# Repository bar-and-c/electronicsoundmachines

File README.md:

# electronicsoundmachines
A collection of stuff related to creating sounds using electronic devices.

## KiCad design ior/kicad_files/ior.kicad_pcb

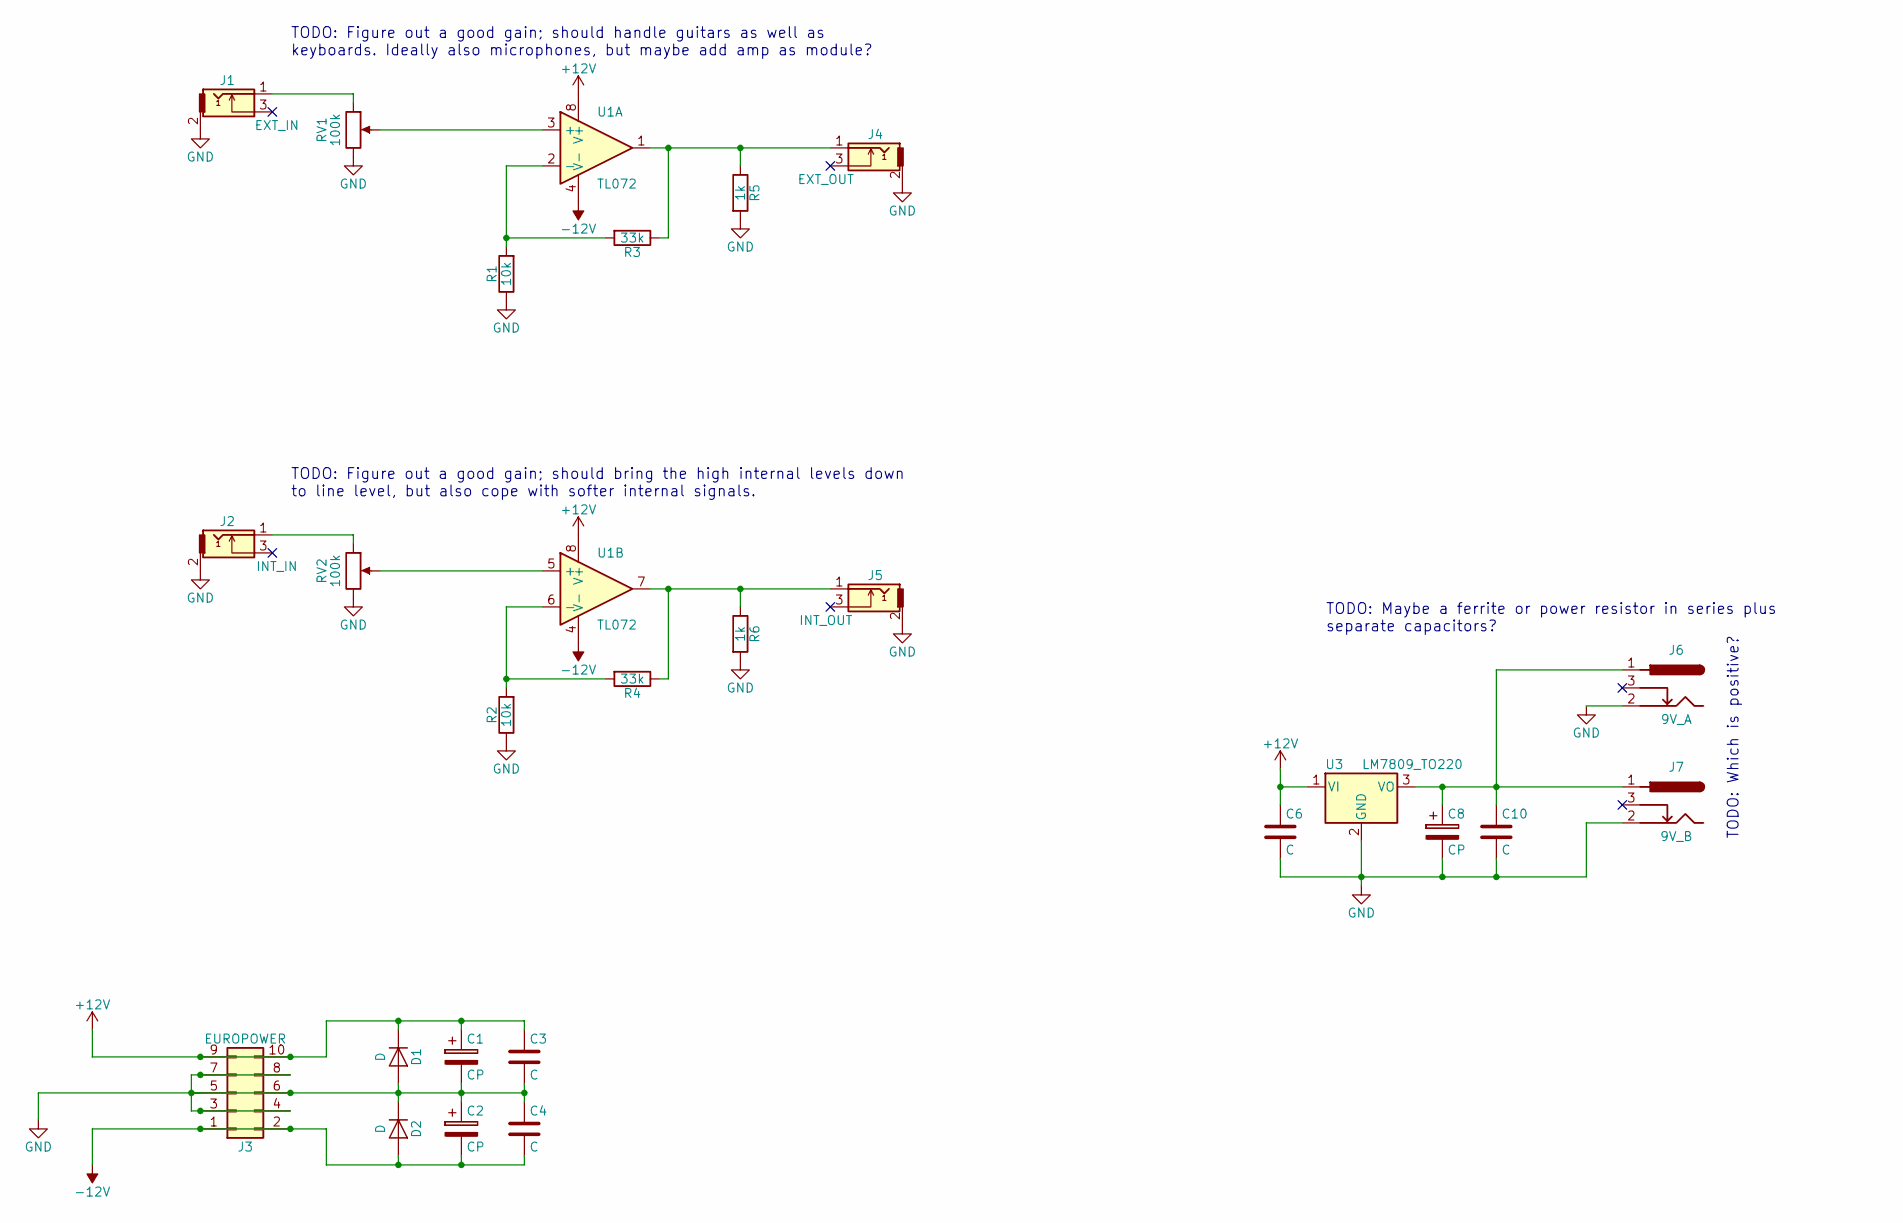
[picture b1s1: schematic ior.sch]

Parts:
C1, C2, C8: CP; CP_Radial_D10.0mm_P2.50mm
C3, C4, C6, C10: C; C_Rect_L7.0mm_W3.5mm_P5.00mm
D1, D2: D; D_DO-35_SOD27_P7.62mm_Horizontal
J1: EXT_IN; Pin_Header_Straight_1x03_Pitch2.54mm
J2: INT_IN; Switchcraft_35RAPC2AV_3_5_mm_jack
J3: EUROPOWER; Pin_Header_Straight_2x05_Pitch2.54mm
J4: EXT_OUT; Switchcraft_35RAPC2AV_3_5_mm_jack
J5: INT_OUT; Pin_Header_Straight_1x03_Pitch2.54mm
J6: 9V_A; BARREL_JACK
J7: 9V_B; BARREL_JACK
R1, R2: 10k; R_Axial_DIN0207_L6.3mm_D2.5mm_P7.62mm_Horizontal
R3, R4: 33k; R_Axial_DIN0207_L6.3mm_D2.5mm_P7.62mm_Horizontal
R5, R6: 1k; R_Axial_DIN0207_L6.3mm_D2.5mm_P7.62mm_Horizontal
RV1, RV2: 100k; Potentiometer_Alps_RK09Y_Vertical
U1: TL072; DIP-8_W7.62mm_Socket_LongPads
U3: LM7809_TO220; TO-220-3_Horizontal

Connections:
+12V: C1.1, C3.1, C6.1, D1.1 (K), J3.9, J3.10, U1.8 (V+), U3.1 (VI)
-12V: C2.2, C4.2, D2.2 (A), J3.1, J3.2, U1.4 (V-)
GND: C1.2, C2.1, C3.2, C4.1, C6.2, C8.2, C10.2, D1.2 (A), D2.1 (K), J1.2, J2.2, J3.3, J3.4, J3.5, J3.6, J3.7, J3.8, J4.2, J5.2, J6.2, J7.2, R1.1, R2.1, R5.2, R6.2, RV1.3, RV2.3, U3.2 (GND)
unnamed: C8.1, C10.1, J6.1, J7.1, U3.3 (VO)
unnamed: J1.1, RV1.1
unnamed: J2.1, RV2.1
unnamed: J4.1, R3.1, R5.1, U1.1
unnamed: J5.1, R4.1, R6.1, U1.7
unnamed: R1.2, R3.2, U1.2 (-)
unnamed: R2.2, R4.2, U1.6 (-)
unnamed: RV1.2, U1.3 (+)
unnamed: RV2.2, U1.5 (+)

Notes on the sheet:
TODO: Which is positive?
TODO: Figure out a good gain; should handle guitars as well as keyboards. Ideally also microphones, but maybe add amp as module?
TODO: Figure out a good gain; should bring the high internal levels down to line level, but also cope with softer internal signals.
TODO: Maybe a ferrite or power resistor in series plus separate capacitors?

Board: 2 copper layers, 26 parts (0 on the bottom side), 12 nets, no tracks yet.

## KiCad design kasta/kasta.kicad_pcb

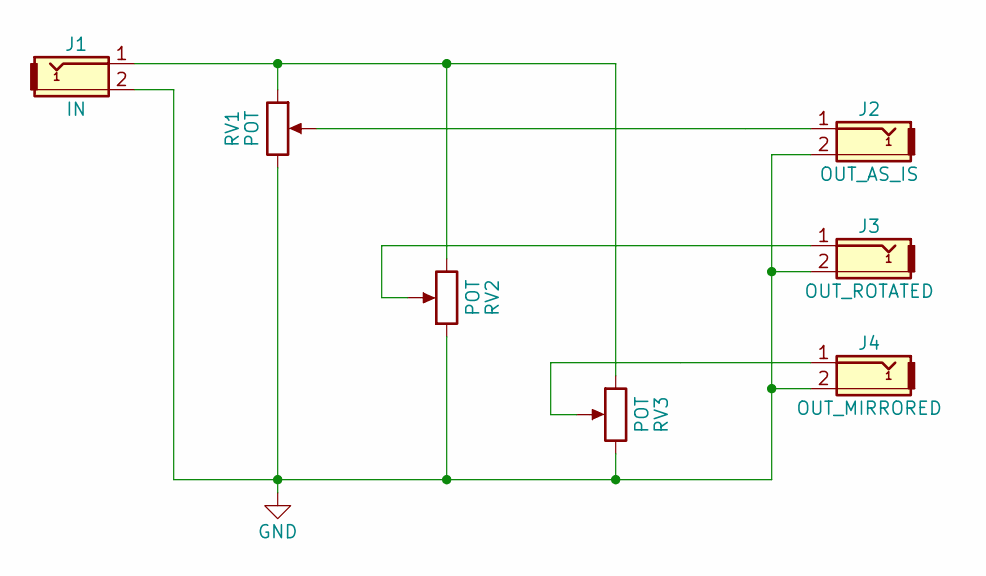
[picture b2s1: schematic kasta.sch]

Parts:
J1: IN; Pin_Header_Straight_1x02_Pitch2.54mm
J2: OUT_AS_IS; Pin_Header_Straight_1x02_Pitch2.54mm
J3: OUT_ROTATED; Pin_Header_Straight_1x02_Pitch2.54mm
J4: OUT_MIRRORED; Pin_Header_Straight_1x02_Pitch2.54mm
RV1, RV2, RV3: POT; Potentiometer_Alps_RK09Y_Vertical

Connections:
GND: J1.2, J2.2, J3.2, J4.2, RV1.3, RV2.1, RV3.3
unnamed: J1.1, RV1.1, RV2.3, RV3.1
unnamed: J2.1, RV1.2
unnamed: J3.1, RV2.2
unnamed: J4.1, RV3.2

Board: 2 copper layers, 7 parts (0 on the bottom side), 5 nets, no tracks yet.

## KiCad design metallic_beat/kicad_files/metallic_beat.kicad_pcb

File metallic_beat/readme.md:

# Metallic Beat

The CR-78 is my favourite drum machine, both the sounds and the patterns (it is like canned musicality), and the cymbal together with metallic beat was the sound(s) I wanted to build first. So far I have only finished the latter. 

The schematic is not completely finished yet, but soundwise it is usable (the final stage will soon be added to the schematic).

In addition to the service manual, lots of inspiration found in <http://electro-music.com/forum/topic-67084-25.html>, especially <http://electro-music.com/forum/phpbb-files/cr78_mb_607.png> (for me, the key to getting that kind of design to work was to lower R566 – I think it was designed to work with a negative trigger pulse).

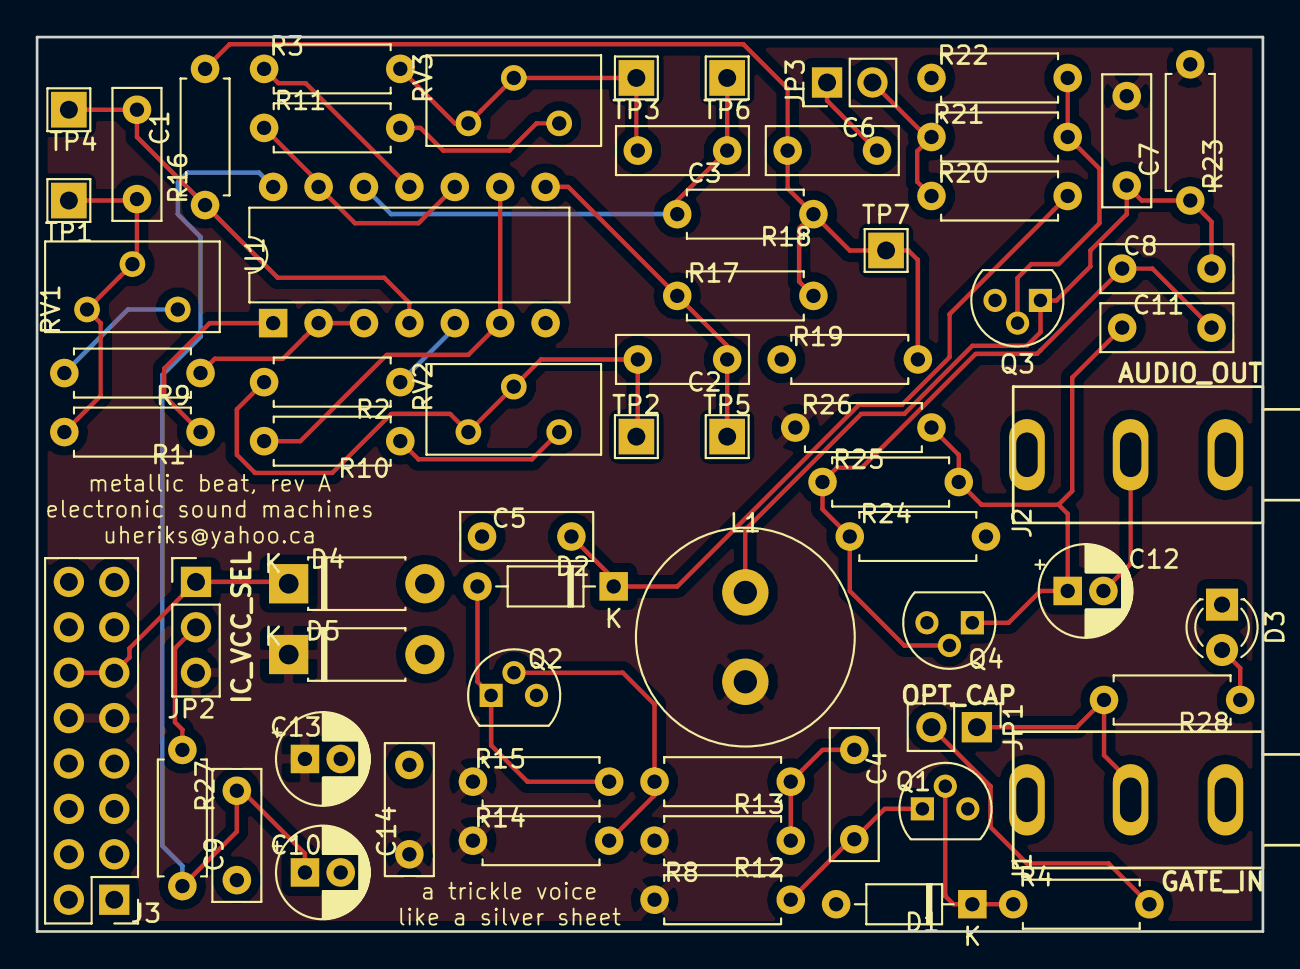
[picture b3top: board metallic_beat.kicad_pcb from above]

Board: 2 copper layers, 68.6 x 50.0 mm, 66 parts (0 on the bottom side), 37 nets.

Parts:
C1: 1.5 nF; C_Rect_L7.2mm_W2.5mm_P5.00mm_FKS2_FKP2_MKS2_MKP2
C2: 1.8 nF; C_Rect_L7.2mm_W2.5mm_P5.00mm_FKS2_FKP2_MKS2_MKP2
C3: 2.2 nF; C_Rect_L7.2mm_W2.5mm_P5.00mm_FKS2_FKP2_MKS2_MKP2
C4: 470 nF; C_Rect_L7.2mm_W2.5mm_P5.00mm_FKS2_FKP2_MKS2_MKP2
C5: 22 nF; C_Rect_L7.2mm_W2.5mm_P5.00mm_FKS2_FKP2_MKS2_MKP2
C6, C7: 15 nF; C_Rect_L7.2mm_W2.5mm_P5.00mm_FKS2_FKP2_MKS2_MKP2
C8: 68nF; C_Rect_L7.2mm_W2.5mm_P5.00mm_FKS2_FKP2_MKS2_MKP2
C9, C14: 100nF; C_Rect_L7.2mm_W2.5mm_P5.00mm_FKS2_FKP2_MKS2_MKP2
C10, C13: 10uF; CP_Radial_D5.0mm_P2.00mm
C11: 100pF; C_Rect_L7.2mm_W2.5mm_P5.00mm_FKS2_FKP2_MKS2_MKP2
C12: 4.7uF; CP_Radial_D5.0mm_P2.00mm
D1, D2: 1N4148; D_DO-35_SOD27_P7.62mm_Horizontal
D3: LOW POWER LED; LED_D3.0mm_FlatTop
D4, D5: 1N4001; D_DO-41_SOD81_P7.62mm_Horizontal
J1: GATE_IN; Switchcraft_35RAPC2AV_3_5_mm_jack_no_switch
J2: AUDIO_OUT; Switchcraft_35RAPC2AV_3_5_mm_jack_no_switch
J3: POWER; PinHeader_2x08_P2.54mm_Vertical
JP1: OPT_CAP; PinHeader_1x02_P2.54mm_Vertical
JP2: IC_VCC_SEL; PinHeader_1x03_P2.54mm_Vertical
JP3: VCA_IN; PinHeader_1x02_P2.54mm_Vertical
L1: 47 mH; L_Radial_D12.0mm_P5.00mm_Fastron_11P
Q1, Q4: BC337; TO-92L
Q2, Q3: BC547; TO-92L
R1, R2, R3, R28: 4.7k; R_Axial_DIN0207_L6.3mm_D2.5mm_P7.62mm_Horizontal
R4: 680; R_Axial_DIN0207_L6.3mm_D2.5mm_P7.62mm_Horizontal
R8: 100k; R_Axial_DIN0207_L6.3mm_D2.5mm_P7.62mm_Horizontal
R9, R10, R11: 39k; R_Axial_DIN0207_L6.3mm_D2.5mm_P7.62mm_Horizontal
R12, R15, R23: 10k; R_Axial_DIN0207_L6.3mm_D2.5mm_P7.62mm_Horizontal
R13: 1k; R_Axial_DIN0207_L6.3mm_D2.5mm_P7.62mm_Horizontal
R14: 820k; R_Axial_DIN0207_L6.3mm_D2.5mm_P7.62mm_Horizontal
R16, R17, R18, R25: 470k; R_Axial_DIN0207_L6.3mm_D2.5mm_P7.62mm_Horizontal
R19: 6.8k; R_Axial_DIN0207_L6.3mm_D2.5mm_P7.62mm_Horizontal
R20: 3.3M; R_Axial_DIN0207_L6.3mm_D2.5mm_P7.62mm_Horizontal
R21: 100K; R_Axial_DIN0207_L6.3mm_D2.5mm_P7.62mm_Horizontal
R22: 270K; R_Axial_DIN0207_L6.3mm_D2.5mm_P7.62mm_Horizontal
R24: 120k; R_Axial_DIN0207_L6.3mm_D2.5mm_P7.62mm_Horizontal
R26: 47k; R_Axial_DIN0207_L6.3mm_D2.5mm_P7.62mm_Horizontal
R27: 47; R_Axial_DIN0207_L6.3mm_D2.5mm_P7.62mm_Horizontal
RV1, RV2, RV3: 20k; Potentiometer_Bourns_3386X_Horizontal
TP1: CAP1; TestPoint_THTPad_2.0x2.0mm_Drill1.0mm
TP2: CAP2; TestPoint_THTPad_2.0x2.0mm_Drill1.0mm
TP3: CAP3; TestPoint_THTPad_2.0x2.0mm_Drill1.0mm
TP4: OSC1; TestPoint_THTPad_2.0x2.0mm_Drill1.0mm
TP5: OSC2; TestPoint_THTPad_2.0x2.0mm_Drill1.0mm
TP6: OSC3; TestPoint_THTPad_2.0x2.0mm_Drill1.0mm
TP7: OSC_OUT; TestPoint_THTPad_2.0x2.0mm_Drill1.0mm
U1: 4069; DIP-14_W7.62mm

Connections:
+5V: D4.1, J3.11, J3.12, JP2.1
+12V: C7.1, C13.1, C14.1, D5.1, J3.9, J3.10, JP2.3, L1.1, R8.1, R12.1, R14.1, R15.1, R23.1, R26.1
GND: C5.1, C9.2, C10.2, C13.2, C14.2, D1.2, D3.1, D4.2, D5.2, J1.2, J2.2, J3.3, J3.4, J3.5, J3.6, J3.7, J3.8, Q1.3, Q2.3, Q3.3, Q4.3, R19.1, R22.2, R24.2, U1.7
unnamed: C1.1, R16.2, TP4.1, U1.4
unnamed: C1.2, R1.2, RV1.1, RV1.2, TP1.1
unnamed: C2.1, R17.2, TP5.1, U1.8
unnamed: C2.2, R2.2, RV2.1, RV2.2, TP2.1
unnamed: C3.1, R18.2, TP6.1, U1.12
unnamed: C3.2, R3.2, RV3.1, RV3.2, TP3.1
unnamed: C4.1, R12.2, R13.2
unnamed: C4.2, Q1.1, R8.2
unnamed: C5.2, D2.1, R20.2
unnamed: C6.1, JP3.1
unnamed: C6.2, R16.1, R17.1, R18.1, R19.2, TP7.1
unnamed: C7.2, C8.2, L1.2, Q3.1, R23.2
unnamed: C9.1, C10.1, R27.2, U1.14
unnamed: C11.1, C12.1, Q4.1, R25.1, R26.2
unnamed: C8.1, C11.2, Q4.2, R24.1, R25.2
unnamed: C12.2, J2.1
unnamed: D1.1, Q1.2, R4.1
unnamed: D2.2, Q2.1, R15.2
unnamed: D3.2, R28.1
unnamed: J1.1, JP1.1, R28.2
unnamed: JP1.2, R4.2
unnamed: JP2.2, R27.1
unnamed: JP3.2, R20.1, R21.2
unnamed: Q2.2, R13.1, R14.2
unnamed: Q3.2, R21.1, R22.1
unnamed: R1.1, U1.1
unnamed: R2.1, U1.5
unnamed: R3.1, U1.11
unnamed: R9.1, U1.2, U1.3
unnamed: R9.2, RV1.3
unnamed: R10.1, U1.6, U1.9
unnamed: R10.2, RV2.3
unnamed: R11.1, U1.10, U1.13
unnamed: R11.2, RV3.3

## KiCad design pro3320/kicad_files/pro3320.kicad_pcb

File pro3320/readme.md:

# pro3320 VCF

This VCF is pretty much only an implementation of the data sheet's reference circuits, with some inspiration taken from the ProOne's schematic. Also, I added four switches, to be able to switch between high pass and low pass filter for each stage.

The things "inspired by" the ProOne include e.g. the OP amp in the resonance chain, and using 150pF instead of 300pF for filter capacitors. The latter shifts the filter frequency one octave up, according to https://electricdruid.net/cem3320-filter-designs/ – try changing them if you feel bold.

I added an optional output after stage two; I figured it would be nice to be be able to get an intermediate signal out (I imagined that would be like a 12dB/octave filter). Something is strange there, though, and I haven't figured out what. It sounds OK without resonance, but with resonance it gets really weird. Quiet. So maybe don't use that output, okay, or be happy using it without resonance?
My uneducated guess is that the resonance feedback is taken from the output, but when tapping from that extra output, the resonance is still taken from the "normal" (24dB/octave) output. I cannot explain what the effect would be as it is, maybe some phase cancellation thing, but that is the only thing I can think of. There are synths that have options like these, see https://electricdruid.net/cem3320-filter-designs/ for examples, and e.g. the Elka Synthex takes the resonance feedback from the actual output.

## Build instructions

### General hints

- If you're using the panel currently in the repo, C1 is too close to the switch SW2, let C1 have a little longer legs than normal, so that you can poke it to the side without force. 
- The jacks are mounted a bit too close to the PCB, risk for contact with pot lugs. Clip the pot lugs (or make another panel design).
- The voltage divider and shit that provides frequency control is a bit off. Possibly because of too high resistance(s), maybe other stuff in parallell is lowering the effective resistance. In any case, either figure out the root cause (which might involve getting other pots), or just experiment to get it as you want (e.g.: if it is as I suspect, that e.g. other impedances in the circuit somehow affect the R1/RV1 voltage divider, then it should be possible to change R1 to something lower instead of changing R1/RV1 to say 12k/10k). I put 100k in parallell with the 120k – thought it might be too much, but it turned out almost OK. The effect in sound, with too little voltage on RV1, is that the filter doesn't open up completely.

## Design woes
After building my first one I quickly realised that I had taken too many shortcuts without thinking when doing the schematic. Things sounded bad, the resonance was dull and strange. On top of that, after measuring to find reasons _why_, suddenly the low pass configuration stopped working altogether – whether because of sloppy measuring damaging the IC, or something else, I do not know. 

What I did discover, though, was that the refernce schematic was designed for +/- 15 volts, and some of the text I skimmed over in a haste the first time through made me realise that most of the resistors in the signal path should have other, lower, values. 

So, this is an attempt to document how I _think_ it should be, for future reference (so that I know what I did, and why).

Alright, first (what I think is) the easy stuff, frequency and resonance control, then on to the slightly more hairy stuff in the signal path. 

### Cutoff frequency control
The frequency control input, pin 12, should be kept between -25mV and 155mV for best results. Also, the in contrast to my intuition, a higher voltage on pin 12 results in a lower filter cutoff. The "absolute maximum ratings" section states that the max voltage between pin 12 and ground is +/-6V. The last fact feels reassuring, it gives a good margin to screw up!
In other words: 
In my schematic, I have one inverting OP-amp stage to convert the incoming CV (as well as the CV from the internal cutoff potentiometer).
The OP-amp stage has an amplification of -0.039, so 0 to 10V in should give 0 to -0.39 volts.

So, the cutoff pot is at the bottom of a voltage divider, making the CV from the pot go from 0 to approx 5.5 volts. With the amplification factor -0.039, that gives roughly 0 to -210mV.

But wait, there's also an offset: a voltage divider that, given the amplification factor, should give a idle voltage of about 250mV on the output, so the internal cutoff pot would give 250mV to 40mV when turning it from low to high cutoff. OK, don't know how I calculated that originally, but hey – it's within reasonable limits. 

The external CV can theoretically be pretty much anything between -12V to 12V, giving an output of approx. 700mV to -200mV, including the offset. Very much outside the "-25mV and 155mV for best results" range, but far from the maximum +/-6V. 

### Resonance control
Maximum limit: +2 to -18 volts to ground. Also, max current for any pin is 40mA.
The control signal is a current input, the input is – as I understand it – virtual ground, meaning the control current can be calculated from the control voltage over the serial resistor (R23 in rev A of the schematic). The resistor should be chosen to give the desired maximum resonance control current at max resonance control voltage. The "desired current" is not obvious (to me); there is a graph, and there is some math, and not until now do I fully understand that I _still_ don't understand how to pick that resistor. Well, guessing is also an option: the reference schematic has 100k for unknown control voltage (but the circuit is based on +/-15V, and for 15V CV, that goves 150uA), the ProOne has 200k for 15V max (giving 75uA). I accidentally envisioned a control voltage between 0-5V and chose 56k to get around 100uA, but for the actual max 12V in, that would give 210uA – which is high, but not freakishly high. Also, for the internal pot, which has a voltage divider giving a range 0-5.4V, giving a control current of 95uA, which is decent.

### Signal path
OK, brace yourself. The chip consists of four pretty much identical blocks of a current-in/current-out "variable gain cell" (the gain control originates from the frequency CV), and a buffer with high input impedance. And then there's a lot of math again. Knock yourself out. Me, I mix fragments of the text in the data sheet with some guesswork, let's see what that gives. 
The math mentions Iref; Iref is also listed in the table of characteristics as 63uA – so it's chip specific. 
The feedback resistor is calculated as (.46 * Vcc - 0.65) / Iref = 77.3k.

[UPDATE: No, Iref is _not_ (necessarily) exactly as listed in the characteristics table: at the top of the table it says Vcc=15V and Rf=100k. Read on.]

Now, here's what I don't understand (one of the things, not the only one): In the text, Iref is said to be (.46 * Vcc - 0.65) / 100k. Further down, Rf is calculated using the same formula, basically: Rf = (.46 * Vcc - 0.65) / Iref. In other words, substituting Iref gives Rf = 100k _always_ (e.g. for all values of Vcc). Feels a bit circular to me. Meanwhile, Iref is also listed in the table of characteristics, with no mention of it being dependent on Vcc (but the text hints that it is). UPDATE: In fact, at the top of the table it says Vcc=15V and Rf=100k. 
It blows my mind. If Iref indeed is calculated as the formula says, with 100k in the denominator, then Rf _is_ 100k, then there's no need to calculate it – but then the data sheet goes on by saying "this is how you calculate Rf". 
It also says "in the simple case of Figure 1 Rf is ...", so maybe that's because it's a simple circuit? For circuits that aren't just a copy of the reference circuit, maybe Rf could be something else?

So, again, I don't know. Either Rf is 73k, or 100k. 

I tried to find other 12V implementations, no big luck: EricaSynths have one, but the schematic is really hard to understand (for me); the Elka Synthex featured in Electric Druid's articles on the 3320 is 12V, and has 82k both for Rf and Rc and 220k for Rb.

The best interpretation I have made is that the 100k used when calculating Iref is something that is defined, something to accept. That is how Iref is calculated. And that Rf just happens to be 100k as well (since it's just a rearrangement of the same Ohm's law) is just because the circuit in fig. 1 is so simple – another design might yield another value for Rf.

If that is the case:
Rf: 100k
Req: 91k
Voltage gain should be 1, and is defined by Req/Rc =>
Rc: 91k
The buffer outputs will be 0.46 * Vcc = 5.5V.
Iref: (5.5 - 0.65) / 100k = 49uA
The total idle current into each stage should be iRef. 
For stage 1, this comes from its Rf.
For stage 2-4:
49uA from Rf, 60uA from Rc from the stage before, so 60uA needs to be discarded through Rb.
Rb = 12 / 60E-6 = 200k

NOTE: I put 2.2M in parallell over the 220k I had already mounted. Sounds OK, but then I'm no expert.

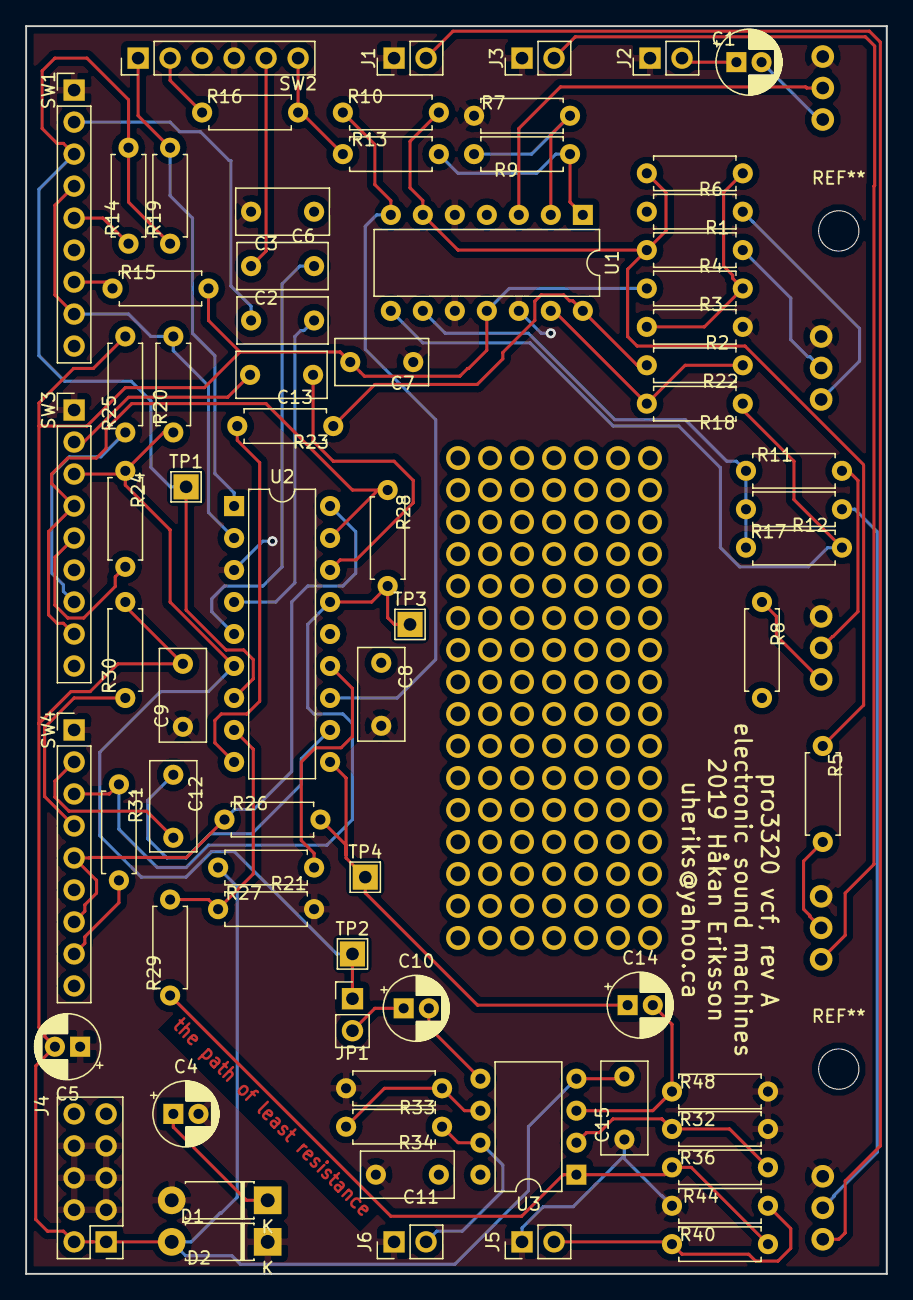
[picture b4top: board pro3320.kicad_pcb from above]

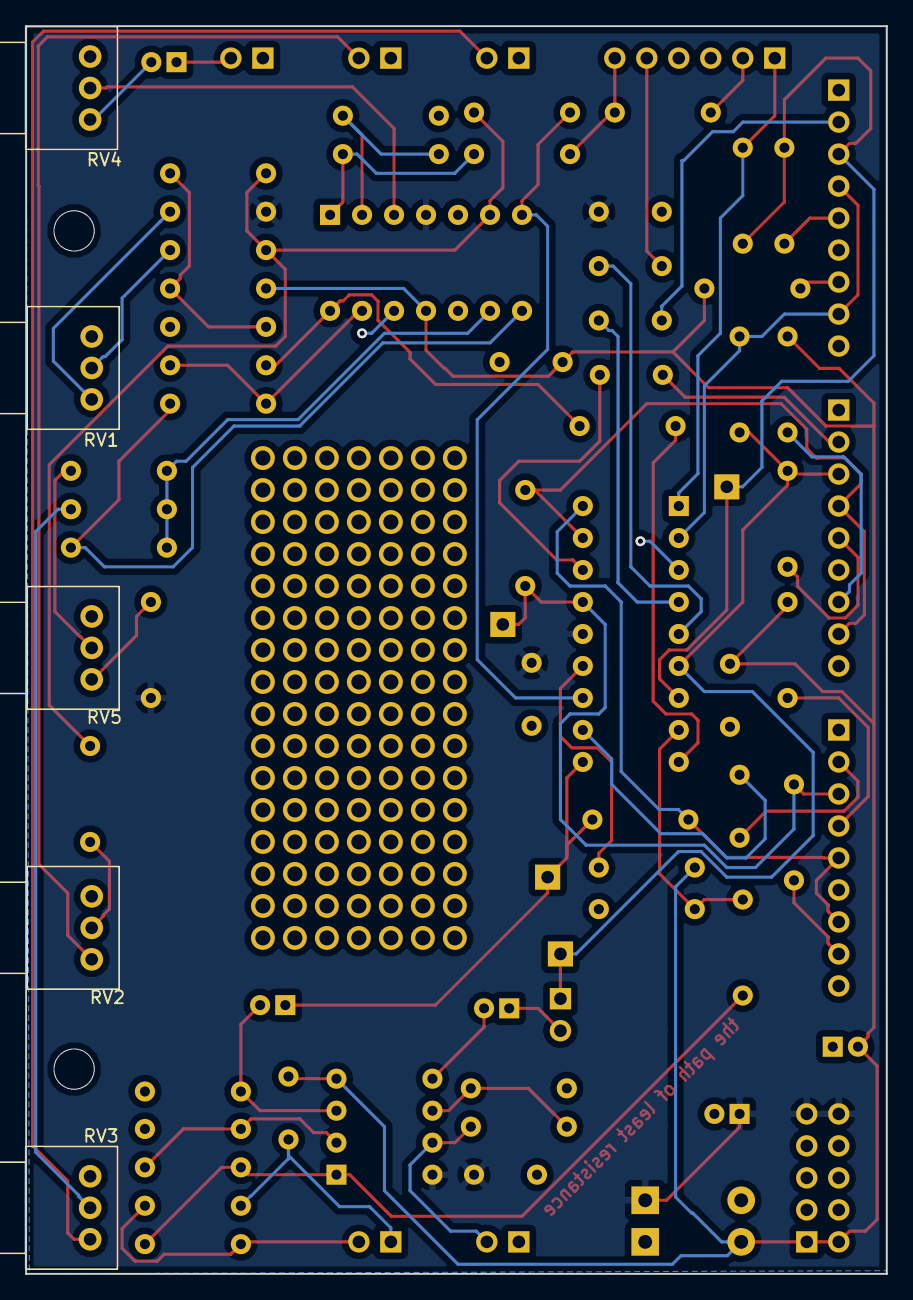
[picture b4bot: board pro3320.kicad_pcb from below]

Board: 2 copper layers, 68.3 x 99.1 mm, 78 parts (5 on the bottom side), 58 nets.

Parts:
C1, C10, C14: 2.2uF; CP_Radial_D5.0mm_P2.00mm
C2, C3, C12, C13: 150p; C_Rect_L7.0mm_W3.5mm_P5.00mm
C4, C5: 10uF; CP_Radial_D5.0mm_P2.00mm
C6, C7, C8, C9, C11, C15: 100nF; C_Rect_L7.2mm_W3.5mm_P5.00mm_FKS2_FKP2_MKS2_MKP2
D1, D2: 1N4001; D_DO-41_SOD81_P7.62mm_Horizontal
J1: RES_CV; PinHeader_1x02_P2.54mm_Vertical
J2: IN; PinHeader_1x02_P2.54mm_Vertical
J3: FREQ_CV; PinHeader_1x02_P2.54mm_Vertical
J4: EUROPOWER; PinHeader_2x05_P2.54mm_Vertical
J5: OUT; PinHeader_1x02_P2.54mm_Vertical
J6: OUT2; PinHeader_1x02_P2.54mm_Vertical
JP1: OPT_OUT2; PinHeader_1x02_P2.54mm_Vertical
R1, R8: 120k; R_Axial_DIN0207_L6.3mm_D2.5mm_P7.62mm_Horizontal
R2, R48: 68k; R_Axial_DIN0207_L6.3mm_D2.5mm_P7.62mm_Horizontal
R3, R23: 56k; R_Axial_DIN0207_L6.3mm_D2.5mm_P7.62mm_Horizontal
R4, R5, R6, R7, R11, R12, R13, R17, R18, R19, R20, R22, R26, R28, R32, R33: 100k; R_Axial_DIN0207_L6.3mm_D2.5mm_P7.62mm_Horizontal
R9, R15, R25, R30: 220k; R_Axial_DIN0207_L6.3mm_D2.5mm_P7.62mm_Horizontal
R10: 3.9k; R_Axial_DIN0207_L6.3mm_D2.5mm_P7.62mm_Horizontal
R14, R16, R24, R31: 91k; R_Axial_DIN0207_L6.3mm_D2.5mm_P7.62mm_Horizontal
R21: 1.2k; R_Axial_DIN0207_L6.3mm_D2.5mm_P7.62mm_Horizontal
R27: 3k; R_Axial_DIN0207_L6.3mm_D2.5mm_P7.62mm_Horizontal
R29: 51k; R_Axial_DIN0207_L6.3mm_D2.5mm_P7.62mm_Horizontal
R34, R36: 240k; R_Axial_DIN0207_L6.3mm_D2.5mm_P7.62mm_Horizontal
R40, R44: 2.2k; R_Axial_DIN0207_L6.3mm_D2.5mm_P7.62mm_Horizontal
RV1, RV2, RV3, RV4, RV5: 100k; Potentiometer_Alps_RK097_Single_Horizontal
SW1: LPHP2; PinHeader_1x09_P2.54mm_Vertical
SW2: LPHP1; PinHeader_1x06_P2.54mm_Vertical
SW3: LPHP3; PinHeader_1x09_P2.54mm_Vertical
SW4: LPHP4; PinHeader_1x09_P2.54mm_Vertical
TP1: OP1; TestPoint_THTPad_2.0x2.0mm_Drill1.0mm
TP2: OP2; TestPoint_THTPad_2.0x2.0mm_Drill1.0mm
TP3: OP3; TestPoint_THTPad_2.0x2.0mm_Drill1.0mm
TP4: OP4; TestPoint_THTPad_2.0x2.0mm_Drill1.0mm
U1: TL074; DIP-14_W7.62mm
U2: AS3320; DIP-18_W7.62mm
U3: TL072; DIP-8_W7.62mm

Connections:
+12V: C4.1, C6.1, C8.1, C11.1, D1.1, J4.9, J4.10, R1.1, R8.2, U1.4, U2.14, U3.8
-12V: C5.2, C7.2, C9.2, C15.2, D2.2, J4.1, J4.2, R3.2, R15.2, R21.1, R25.2, R30.2, U1.11, U3.4
GND: C4.2, C5.1, C6.2, C7.1, C8.2, C9.1, C11.2, C15.1, D1.2, D2.1, J1.1, J2.1, J3.1, J4.3, J4.4, J4.5, J4.6, J4.7, J4.8, J5.1, J6.1, R2.1, R7.1, R27.2, R32.2, R33.2, R44.1, R48.2, RV1.1, RV2.1, RV3.1, RV4.1, RV5.1, SW1.1, SW2.4, SW3.1, SW4.1, U1.5, U1.10, U1.12, U2.3
unnamed: C1.1, J2.2
unnamed: C1.2, RV4.3
unnamed: C2.1, U2.4
unnamed: C2.2, SW1.2
unnamed: C3.1, U2.5
unnamed: C3.2, SW2.5
unnamed: C10.1, JP1.2
unnamed: C10.2, U3.5
unnamed: C12.1, U2.11
unnamed: C12.2, SW4.2
unnamed: C13.1, SW3.2
unnamed: C13.2, U2.16
unnamed: C14.1, R26.2, TP4.1, U2.10
unnamed: C14.2, R48.1, U3.3
unnamed: J1.2, RV3.3
unnamed: J3.2, RV2.3
unnamed: J5.2, R40.1, R44.2
unnamed: J6.2, R34.1, U3.7
unnamed: JP1.1, R20.1, R24.1, SW3.3, TP2.1, U2.6
unnamed: R1.2, RV1.3
unnamed: R2.2, R3.1, R6.1
unnamed: R4.1, RV1.2
unnamed: R5.1, RV2.2
unnamed: R7.2, R9.2, U1.2
unnamed: R8.1, RV5.3
unnamed: R10.1, U1.7, U2.12
unnamed: R4.2, R5.2, R6.2, R10.2, U1.6
unnamed: R11.1, RV5.2
unnamed: R11.2, R12.2, R17.1, U1.9
unnamed: R12.1, RV3.2
unnamed: R13.1, R16.2, SW2.6
unnamed: R9.1, R13.2, U1.1
unnamed: R14.1, SW1.5
unnamed: R14.2, R19.1, SW1.3, TP1.1, U2.7
unnamed: R15.1, SW1.7
unnamed: R16.1, SW2.2
unnamed: R17.2, R18.1, U1.8
unnamed: R18.2, R22.2, U1.13
unnamed: R19.2, SW2.1, U2.1
unnamed: R20.2, SW1.4, SW1.8, U2.2
unnamed: R21.2, U2.13
unnamed: R22.1, R23.2, U1.14
unnamed: R23.1, U2.9
unnamed: R24.2, SW3.5
unnamed: R25.1, SW3.7
unnamed: R26.1, SW4.5, SW4.7, U2.18
unnamed: R27.1, R29.2, U2.8
unnamed: R28.1, SW3.4, SW3.8, U2.17
unnamed: R28.2, R31.1, SW4.3, TP3.1, U2.15
unnamed: R29.1, R36.1, R40.2, U3.1
unnamed: R30.1, SW4.4
unnamed: R31.2, SW4.8
unnamed: R32.1, R36.2, U3.2
unnamed: R33.1, R34.2, U3.6
unnamed: RV4.2, U1.3

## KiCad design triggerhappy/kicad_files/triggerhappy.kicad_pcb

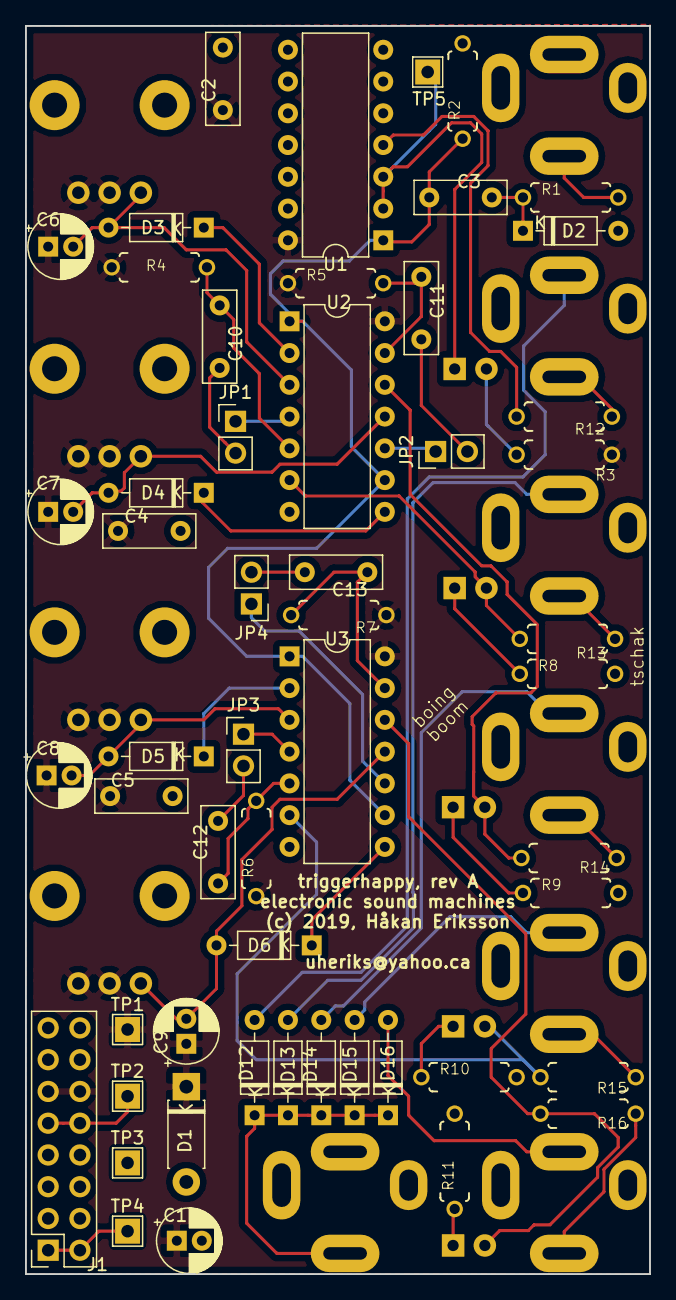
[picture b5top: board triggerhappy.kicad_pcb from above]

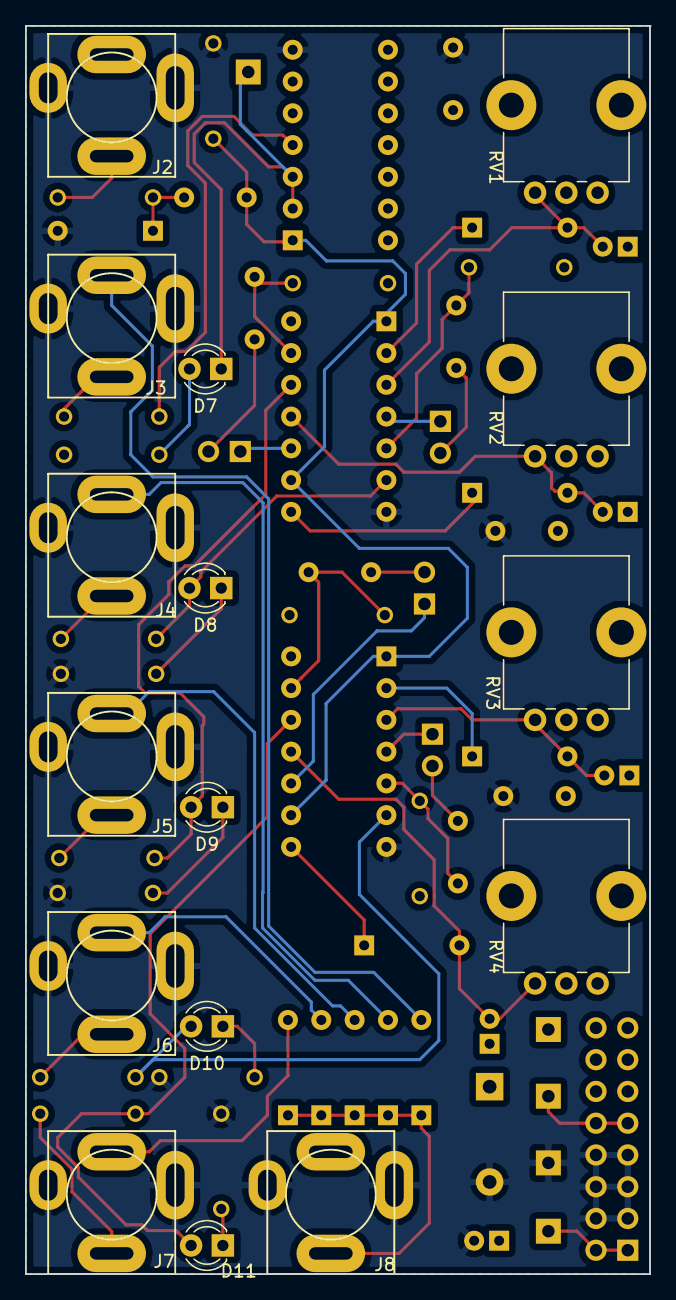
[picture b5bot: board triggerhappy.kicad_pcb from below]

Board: 2 copper layers, 49.9 x 99.8 mm, 69 parts (16 on the bottom side), 49 nets.

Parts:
C1, C6, C7, C8, C9: 10u; CP_Radial_D5.0mm_P2.00mm
C2, C3, C4, C5, C10, C11, C12, C13: 100n; C_Rect_L7.2mm_W2.5mm_P5.00mm_FKS2_FKP2_MKS2_MKP2
D1: 1N4001; D_DO-41_SOD81_P7.62mm_Horizontal
D2: BZX55C5V1; D_DO-35_SOD27_P7.62mm_Horizontal
D3, D4, D5, D6, D12, D13, D14, D15, D16: BAT42; D_DO-35_SOD27_P7.62mm_Horizontal
D7, D8, D9, D10, D11: LED; LED_D3.0mm
J1: EUROPOWER; PinSocket_2x08_P2.54mm_Vertical
J2: GATE_IN; PJ301BM_NO_SWITCH
J3: TRIG_1; PJ301BM
J4: TRIG_2; PJ301BM
J5: TRIG_3; PJ301BM
J6: TRIG_4; PJ301BM
J7: TRIG_5; PJ301BM
J8: TRIG_MIX; PJ301BM_NO_SWITCH
JP1: MONO_OUT_2; PinHeader_1x02_P2.54mm_Vertical
JP2: MONO_OUT_3; PinHeader_1x02_P2.54mm_Vertical
JP3: MONO_OUT_4; PinHeader_1x02_P2.54mm_Vertical
JP4: MONO_OUT_5; PinHeader_1x02_P2.54mm_Vertical
R1: 120; 7MM_RESISTOR
R2, R4, R5, R6, R7: 330k; 7MM_RESISTOR
R3, R8, R9, R10, R11: 1k; 7MM_RESISTOR
R12, R13, R14, R15, R16: 330; 7MM_RESISTOR
RV1, RV2, RV3, RV4: 100k; Potentiometer_Alps_RK09K_Single_Vertical
TP1: 5V; TestPoint_THTPad_2.0x2.0mm_Drill1.0mm
TP2: 12V; TestPoint_THTPad_2.0x2.0mm_Drill1.0mm
TP3: GND; TestPoint_THTPad_2.0x2.0mm_Drill1.0mm
TP4: -12V; TestPoint_THTPad_2.0x2.0mm_Drill1.0mm
TP5: DIR_INV; TestPoint_THTPad_2.0x2.0mm_Drill1.0mm
U1, U2, U3: 40106-pwr; DIP-14_W7.62mm

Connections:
+5V: C1.1, C2.1, C4.1, C5.1, C6.1, C7.1, C8.1, C9.1, D1.1, J1.11, J1.12, R3.1, R4.1, R5.1, R6.1, R7.1, RV1.1, RV1.2, RV2.1, RV2.2, RV3.1, RV3.2, RV4.1, RV4.2, TP1.1, U1.14, U2.14, U3.14
+12V: J1.9, J1.10, TP2.1
-12V: J1.1, J1.2, TP4.1
GND: C1.2, C2.2, C4.2, C5.2, D1.2, D2.2, J1.3, J1.4, J1.5, J1.6, J1.7, J1.8, J2.1, J3.1, J4.1, J5.1, J6.1, J7.1, J8.1, R2.2, R8.2, R9.2, R10.2, R11.2, TP3.1, U1.7, U2.7, U3.7
unnamed: C3.1, R2.1, U1.1, U2.1, U2.9, U3.1, U3.9
unnamed: C3.2, D2.1, R1.1
unnamed: C6.2, D3.2, RV1.3, U2.3
unnamed: C7.2, D4.2, RV2.3, U2.11
unnamed: C8.2, D5.2, RV3.3, U3.3
unnamed: C9.2, D6.2, RV4.3, U3.11
unnamed: C10.1, R4.2, U2.5
unnamed: C10.2, JP1.2
unnamed: C11.1, R5.2, U2.13
unnamed: C11.2, JP2.2
unnamed: C12.1, R6.2, U3.5
unnamed: C12.2, JP3.2
unnamed: C13.1, R7.2, U3.13
unnamed: C13.2, JP4.2
unnamed: D3.1, U2.2
unnamed: D4.1, U2.8
unnamed: D5.1, U3.2
unnamed: D6.1, U3.8
unnamed: D7.1, TP5.1, U1.2, U1.3
unnamed: D7.2, R3.2
unnamed: D8.1, R8.1
unnamed: D8.2, R13.2, U2.6
unnamed: D9.1, R9.1
unnamed: D9.2, R14.2, U2.12
unnamed: D10.1, R10.1
unnamed: D10.2, R15.2, U3.6
unnamed: D11.1, R11.1
unnamed: D11.2, R16.2, U3.12
unnamed: D12.1, D13.1, D14.1, D15.1, D16.1, J8.2
unnamed: D12.2, J3.2
unnamed: D13.2, J4.2
unnamed: D14.2, J5.2
unnamed: D15.2, J6.2
unnamed: D16.2, J7.2
unnamed: J2.2, R1.2
unnamed: J3.3, R12.1
unnamed: J4.3, R13.1
unnamed: J5.3, R14.1
unnamed: J6.3, R15.1
unnamed: J7.3, R16.1
unnamed: JP1.1, U2.4
unnamed: JP2.1, U2.10
unnamed: JP3.1, U3.4
unnamed: JP4.1, U3.10
unnamed: R12.2, U1.4

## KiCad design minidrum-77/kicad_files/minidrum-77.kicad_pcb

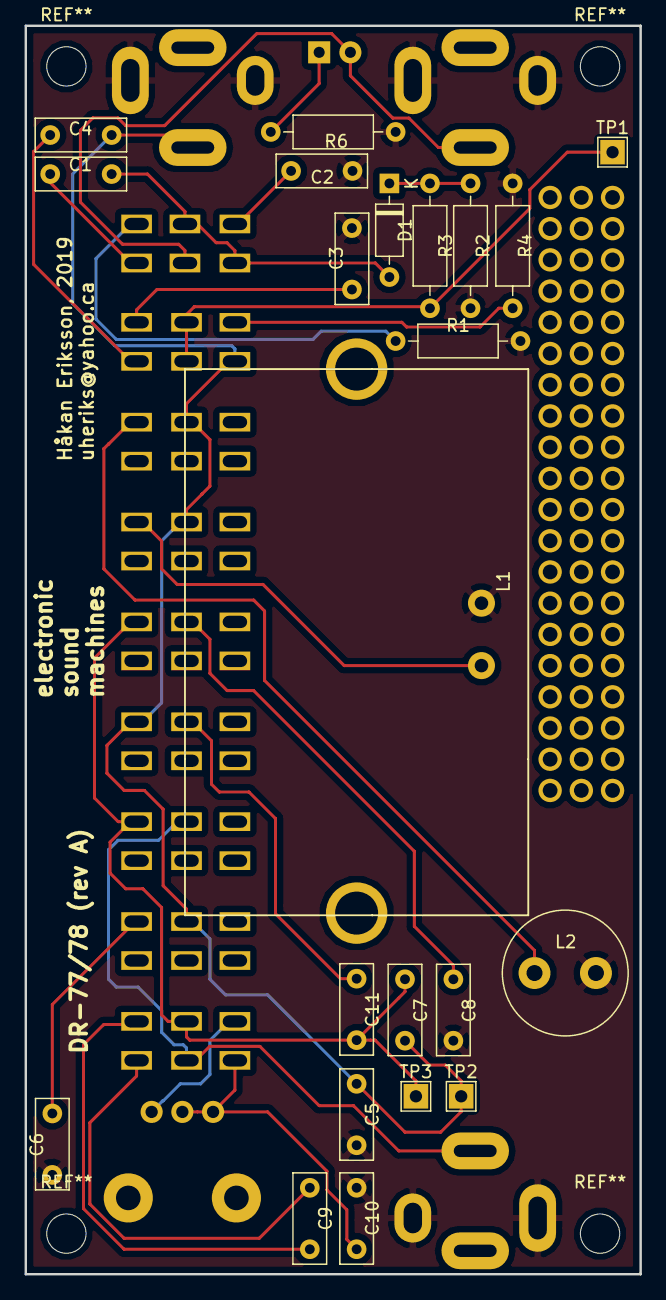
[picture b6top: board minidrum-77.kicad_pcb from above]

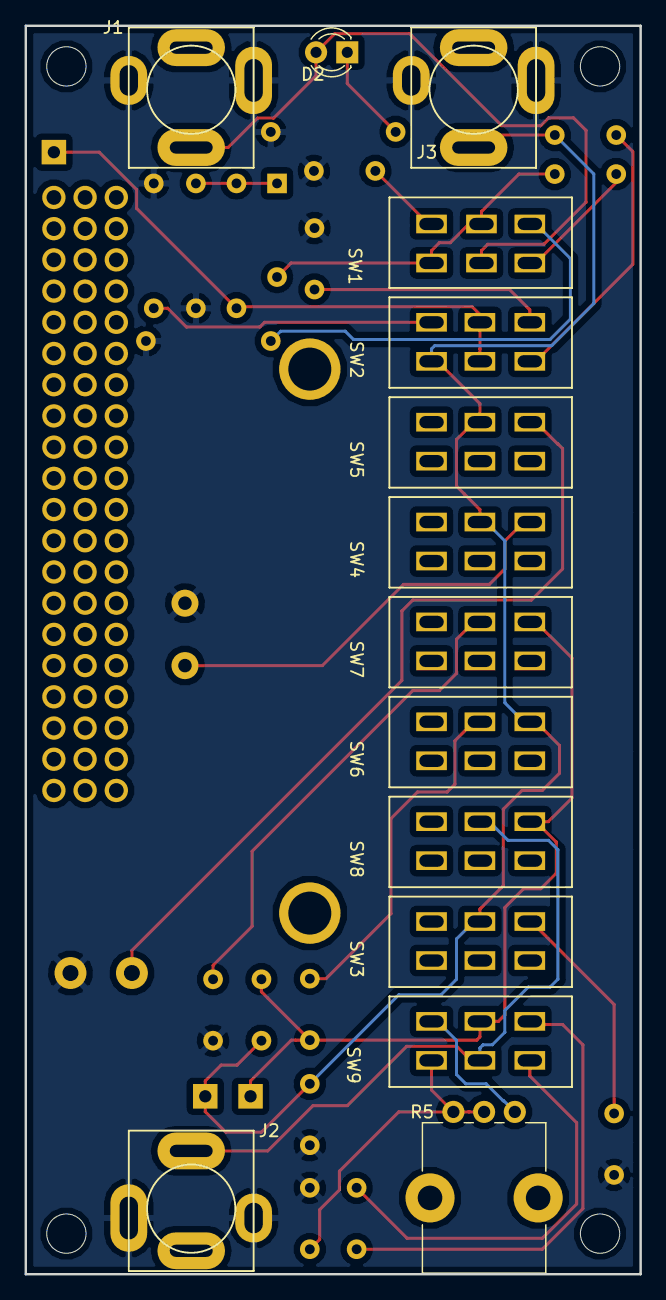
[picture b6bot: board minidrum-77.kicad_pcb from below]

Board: 2 copper layers, 50.0 x 101.6 mm, 36 parts (14 on the bottom side), 24 nets.

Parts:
C1, C2, C3, C4, C5, C6, C7, C8, C9, C10, C11: C_Rect_L7.2mm_W2.5mm_P5.00mm_FKS2_FKP2_MKS2_MKP2
D1: D_DO-35_SOD27_P7.62mm_Horizontal
D2: LED_ALT; LED_D3.0mm
J1: TRIG_IN; PJ301BM
J2: AUDIO_OUT; PJ301BM
J3: EXT_COIL; PJ301BM
L1: CoilC-1X
L2: L_Radial_D10.0mm_P5.00mm_Fastron_07P
R1, R2, R3, R4, R6: R_Axial_DIN0207_L6.3mm_D2.5mm_P10.16mm_Horizontal
R5: CUTOFF; Potentiometer_Alps_RK09K_Single_Vertical
SW1: LPF/HPF_IN; DPDT_PUSH_SW
SW2: RS/C; DPDT_PUSH_SW
SW3: C6_SEL; DPDT_AS_SPST_PUSH_SW
SW4: COIL_1; DPDT_AS_SPST_PUSH_SW
SW5: COIL_2; DPDT_AS_SPST_PUSH_SW
SW6: C11_SEL; DPDT_AS_SPST_PUSH_SW
SW7: C8_SEL; DPDT_AS_SPST_PUSH_SW
SW8: STR_OUT; DPDT_AS_SPST_PUSH_SW
SW9: LPF/HPF_OUT; DPDT_PUSH_SW
TP1, TP2, TP3: TestPoint_THTPad_2.0x2.0mm_Drill1.0mm

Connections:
GND: C2.2, C3.2, C5.2, C6.2, C8.2, C10.2, J1.1, J2.1, J3.1, L1.2, L2.2, R1.2, R2.2, R4.2, R6.2
unnamed: C1.1, D1.2, SW1.1, SW1.5
unnamed: C1.2, SW1.3
unnamed: C2.1, SW1.4
unnamed: C3.1, SW2.1
unnamed: C4.1, C5.1, C7.2, J3.3, SW2.6, SW3.2, SW4.2, SW5.2, SW6.1, TP2.1
unnamed: C4.2, SW2.4
unnamed: C6.1, SW3.1
unnamed: C8.1, SW7.2
unnamed: C9.1, SW9.1
unnamed: C9.2, SW9.4
unnamed: C10.1, R5.1, R5.2, SW9.6
unnamed: C7.1, C11.1, SW7.1, SW8.1, SW9.2, TP3.1
unnamed: C11.2, SW6.2
unnamed: D1.1, R2.1, R3.2
unnamed: D2.1, R6.1
unnamed: D2.2, J1.3, SW1.2
unnamed: J2.3, SW8.2, SW9.5
unnamed: L1.1, SW4.1
unnamed: L2.1, SW5.1
unnamed: R1.1, SW1.6
unnamed: R3.1, SW2.2, SW2.5, TP1.1
unnamed: R4.1, SW2.3
unnamed: R5.3, SW9.3

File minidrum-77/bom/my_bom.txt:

BD:
C2: 4.7 nF
C3: 56 nF
C4: 33 nF
C6: 220 nF
C7: 33 nF
C8: 100 nF
C10: 220 nF
R2: 4.7M
R3: 33k
R5: 10 k
D1: BAT42
L1: 16 H

Claves/RS misch-masch:
C1: 27nF
R1: 270k
R4: 47k
C5: 4.7nF (or 27nF?)
L2: 1.5H
C11: 250pF (or 1nF?)
C9: 1nF

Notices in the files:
mini-lpg/kicad_files/minilpg.kicad_pcb:
(c) 2018 Håkan Eriksson
triggerhappy/kicad_files/triggerhappy.kicad_pcb:
(c) 2019, Håkan Eriksson
